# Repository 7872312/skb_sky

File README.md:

https://github.com/user-attachments/assets/9f682704-2d4a-4023-85d9-843de5016783

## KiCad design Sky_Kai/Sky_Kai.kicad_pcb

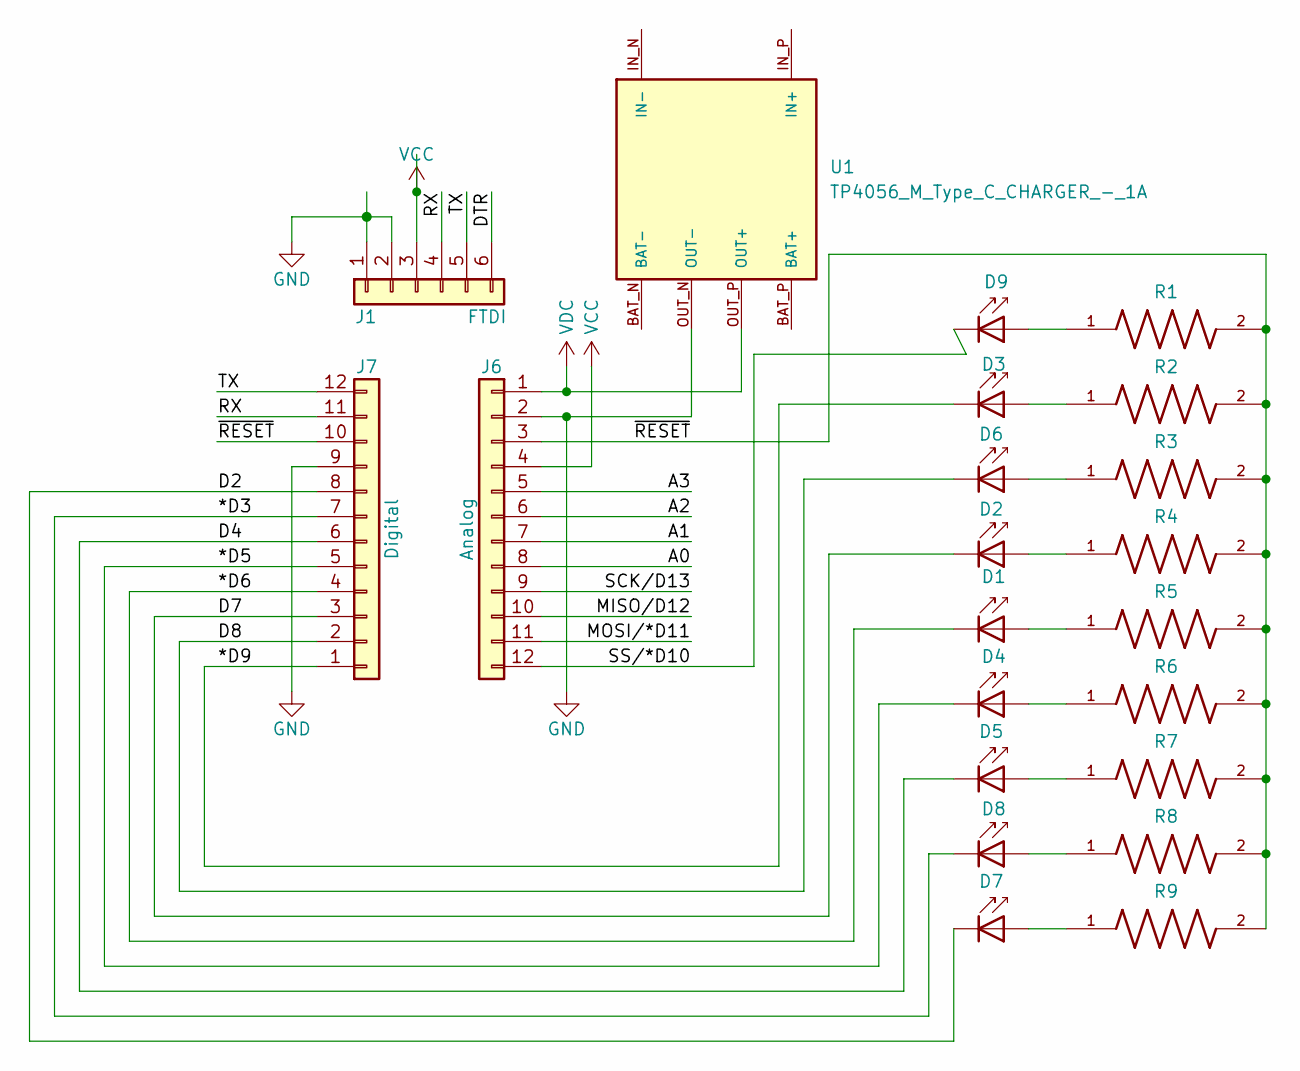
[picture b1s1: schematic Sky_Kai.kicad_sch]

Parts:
D1, D2, D3, D4, D5, D6, D7, D8, D9: LD271; LED_D5.0mm_IRGrey
J1: FTDI; PinHeader_1x06_P2.54mm_Horizontal
J6: Analog; PinHeader_1x12_P2.54mm_Vertical
J7: Digital; PinHeader_1x12_P2.54mm_Vertical
R1, R2, R3, R4, R5, R6, R7, R8, R9: ERJU02F2490X; RES_ERJU02F2490X; MPN ERJU02F2490X
U1: TP4056_M_Type_C_CHARGER_-_1A; MODULE_TP4056_MICRO-USB_CHARGER_-_1A; MPN TP4056 Micro-USB Charger - 1A

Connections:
/*D3: D8.1 (K), J7.7
/*D5: D4.1 (K), J7.5
/*D6: D1.1 (K), J7.4
/*D9: D3.1 (K), J7.1
/A0: J6.8
/A1: J6.7
/A2: J6.6
/A3: J6.5
/D2: D7.1 (K), J7.8
/D4: D5.1 (K), J7.6
/D7: D2.1 (K), J7.3
/D8: D6.1 (K), J7.2
/DTR: J1.6
/MISO/D12: J6.10
/MOSI/*D11: J6.11
/RX: J1.4, J7.11
/SCK/D13: J6.9
/SS/*D10: D9.1 (K), J6.12
/TX: J1.5, J7.12
/~RESET: J6.3, J7.10, R1.2, R2.2, R3.2, R4.2, R5.2, R6.2, R7.2, R8.2, R9.2
GND: J1.1, J1.2, J6.2, J7.9, U1.OUT_N (OUT-)
unnamed: D1.2 (A), R5.1
unnamed: D2.2 (A), R4.1
unnamed: D3.2 (A), R2.1
unnamed: D4.2 (A), R6.1
unnamed: D5.2 (A), R7.1
unnamed: D6.2 (A), R3.1
unnamed: D7.2 (A), R9.1
unnamed: D8.2 (A), R8.1
unnamed: D9.2 (A), R1.1
VCC: J1.3, J6.4
VDC: J6.1, U1.OUT_P (OUT+)

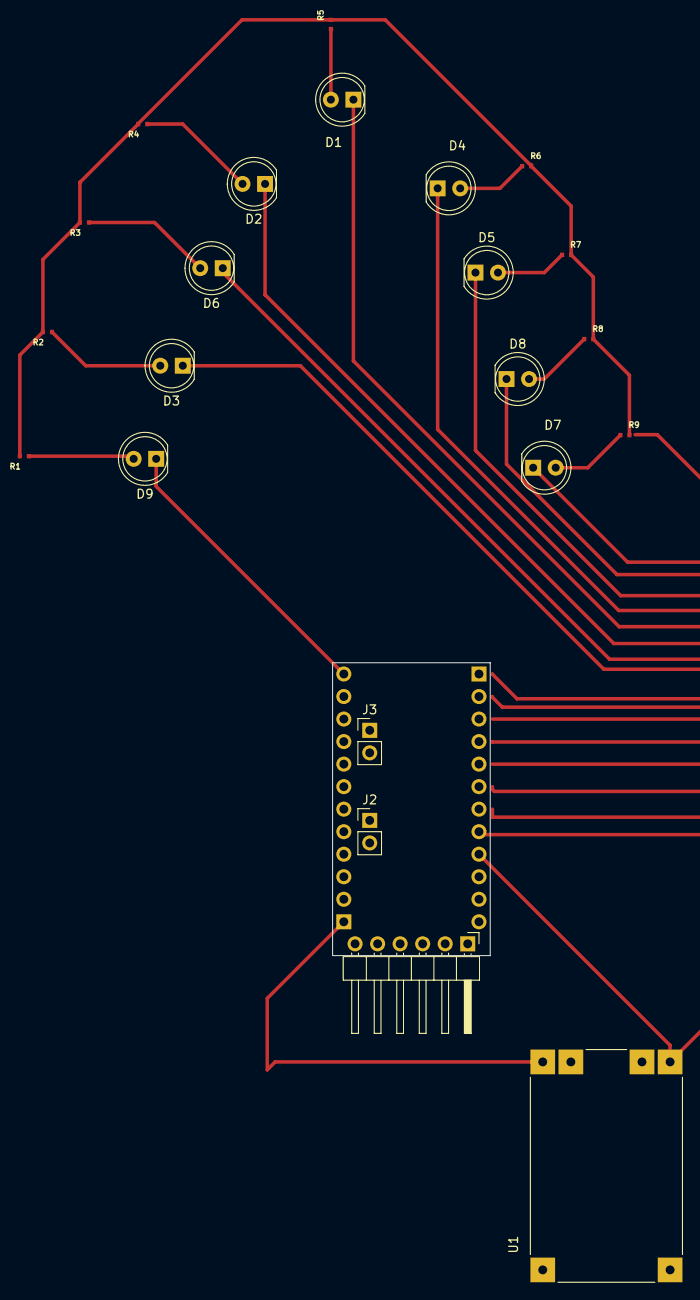
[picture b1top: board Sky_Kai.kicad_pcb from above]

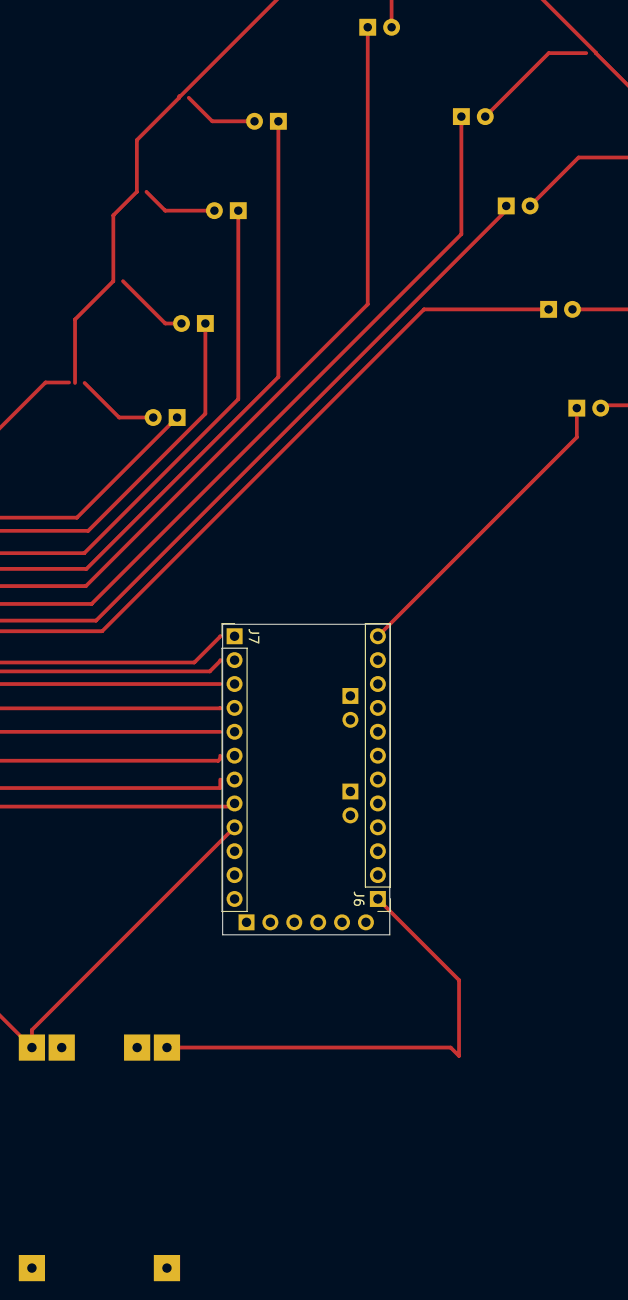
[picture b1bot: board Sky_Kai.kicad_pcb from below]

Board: 2 copper layers, 24 parts (2 on the bottom side), 24 nets.

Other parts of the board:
J2: I2C; PinHeader_1x02_P2.54mm_Vertical
J3: Analog; PinHeader_1x02_P2.54mm_Vertical
